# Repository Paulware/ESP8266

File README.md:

ESP8266
=======

All things related to ESP8266 low cost device

ESP8266.ino is a mega sketch to show basic server capability.

Basic theory of UDP operation:
==============================
   Android device sends out a UDP broadcast to local network (i.e. 192.168.0.255).  The message is "findkey" where key is a unique name of the device (i.e. garageDoor).
   
   All units will receive this message but only the unit with the matching key will respond.  The matching unit will respond: "CTS" (clear to send).
   
   When the android device receives this message it now also has the ip address of the device.  All further communication will  be directly from the android device to the specific ip address of the desired unit.

   The unit will now respond to commands, like "open" or "readTemp".

Useful files/directories:
=========================
Schematics/ESP8266Tiny: An Eagle schematic to create a small pcb that holds an atmega328 and ESP8266 connected to D11/D12<br>
The ESP8266 should be running at baud rate 9600.
ssid and password are stored in EEPROM on the atmega328
A serial based menu allows the user to set ssid/password/and unique key which identifies the ESP8266 on the local network

<hr>
<table>
<tr><th>Videos</th></tr>
<tr><td>smart car <a href="https://www.youtube.com/watch?v=Go8Tyr9nKlo&feature=youtu.be">video</a></td></tr>
</table>

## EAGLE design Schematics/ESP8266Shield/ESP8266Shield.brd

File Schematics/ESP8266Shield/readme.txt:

10/23/2014
   Created ready for ordering
11/10/2014
   D0 was driving ESPTX incorrectly.  This was corrected not ordered yet.
1/7/2014
   D12 is now soft-serial receive and D11 is now soft-serial tx
   Have not ordered or verified yet.

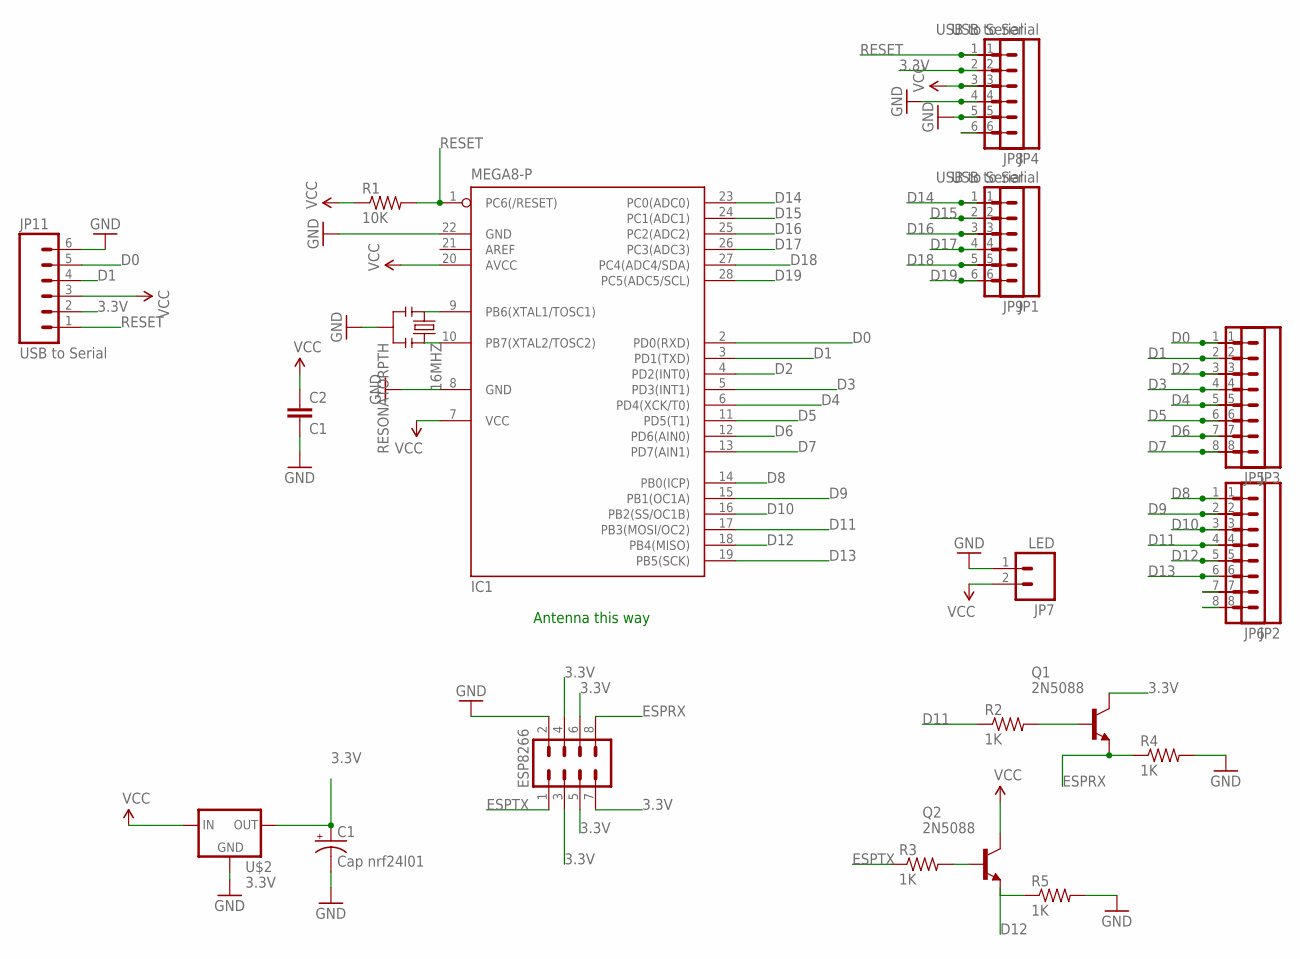
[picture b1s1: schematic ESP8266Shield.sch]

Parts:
16MHZ: RESONATORPTH; RESONATOR-PTH
C1: Cap nrf24l01; CPOL-RADIAL-10UF-25V
C2: C1; CAP-PTH-SMALL
ESP8266: M04X2; 2X4
IC1: MEGA8-P; DIL28-3
JP1, JP4, JP8, JP9, JP11: USB to Serial; 1X06
JP2, JP3, JP5, JP6: M08; 1X08
JP7: LED; 1X02
Q1, Q2: 2N5088; TO92
R1: 10K; AXIAL-0.3
R2, R3, R4, R5: 1K; AXIAL-0.3
U$2: 3.3V; 78XXL

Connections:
3.3V: C1.1 (+), ESP8266.3, ESP8266.4, ESP8266.5, ESP8266.6, ESP8266.7, JP4.2, JP8.2, JP11.2, Q1.1 (C), U$2.GND (OUT)
D0: IC1.2 (PD0(RXD)), JP3.1, JP5.1, JP11.5, Q2.3 (E), R5.P$1 (1)
D1: IC1.3 (PD1(TXD)), JP3.2, JP5.2, JP11.4
D2: IC1.4 (PD2(INT0)), JP3.3, JP5.3
D3: IC1.5 (PD3(INT1)), JP3.4, JP5.4
D4: IC1.6 (PD4(XCK/T0)), JP3.5, JP5.5
D5: IC1.11 (PD5(T1)), JP3.6, JP5.6
D6: IC1.12 (PD6(AIN0)), JP3.7, JP5.7
D7: IC1.13 (PD7(AIN1)), JP3.8, JP5.8
D8: IC1.14 (PB0(ICP)), JP2.1, JP6.1
D9: IC1.15 (PB1(OC1A)), JP2.2, JP6.2
D10: IC1.16 (PB2(SS/OC1B)), JP2.3, JP6.3
D11: IC1.17 (PB3(MOSI/OC2)), JP2.4, JP6.4, R2.P$1 (1)
D12: IC1.18 (PB4(MISO)), JP2.5, JP6.5
D13: IC1.19 (PB5(SCK)), JP2.6, JP6.6
D14: IC1.23 (PC0(ADC0)), JP1.1, JP9.1
D15: IC1.24 (PC1(ADC1)), JP1.2, JP9.2
D16: IC1.25 (PC2(ADC2)), JP1.3, JP9.3
D17: IC1.26 (PC3(ADC3)), JP1.4, JP9.4
D18: IC1.27 (PC4(ADC4/SDA)), JP1.5, JP9.5
D19: IC1.28 (PC5(ADC5/SCL)), JP1.6, JP9.6
ESPRX: ESP8266.8, Q1.3 (E), R4.P$1 (1)
ESPTX: ESP8266.1, R3.P$1 (1)
GND: 16MHZ.2, C1.2 (-), C2.2, ESP8266.2, IC1.8 (GND), IC1.22 (GND), JP4.4, JP4.5, JP7.1, JP8.4, JP8.5, JP11.6, R4.P$2 (2), R5.P$2 (2), U$2.IN (GND)
unnamed: 16MHZ.3, IC1.10 (PB7(XTAL2/TOSC2))
unnamed: 16MHZ.1, IC1.9 (PB6(XTAL1/TOSC1))
unnamed: Q1.2 (B), R2.P$2 (2)
unnamed: Q2.2 (B), R3.P$2 (2)
unnamed: JP2.7, JP6.7
unnamed: JP2.8, JP6.8
unnamed: JP4.6, JP8.6
RESET: IC1.1 (PC6(/RESET)), JP4.1, JP8.1, JP11.1, R1.P$2 (2)
VCC: C2.1, IC1.7 (VCC), IC1.20 (AVCC), JP4.3, JP7.2, JP8.3, JP11.3, Q2.1 (C), R1.P$1 (1), U$2.OUT (IN)

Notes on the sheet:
Antenna this way

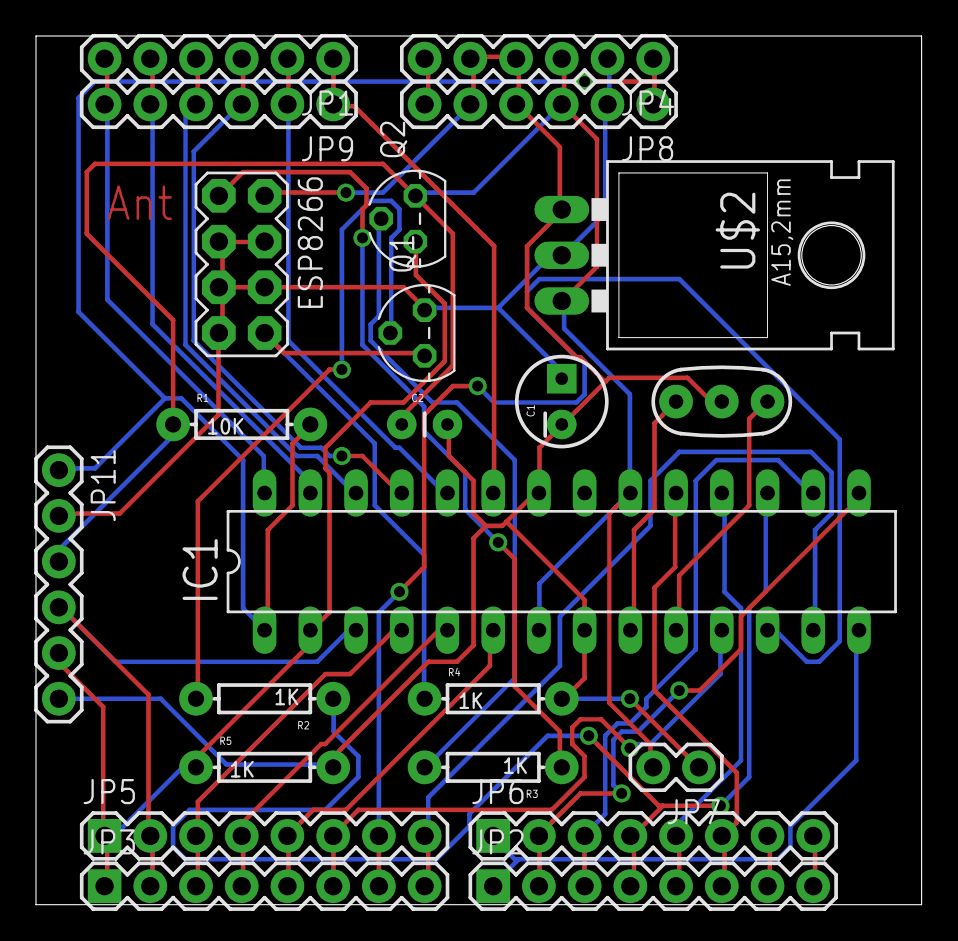
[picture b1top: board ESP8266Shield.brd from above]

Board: 2 copper layers, 49.2 x 48.3 mm, 23 parts (0 on the bottom side), 33 nets.

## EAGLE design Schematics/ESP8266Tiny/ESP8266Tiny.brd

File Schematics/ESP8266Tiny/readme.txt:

10/19/2014
   Created
   Not sure whether the LM 3.3V voltage regulator can provide enough for the ESP8266
   Added a 3.3V Pinout so that an external 3.3V Power source can be provided.
   Will order after testing out the ESP8266 Rx/Tx lines are connected to Arduino
     Rx/Tx so ESP8266 module should be removed will programming.     
   Could be a useful module for an I2C component.
   
10/21/2014
   Confirmed LM 3.3V regulator does indeed provide enough power for this device.
   Transistors were added so that the 5V arduino can communicate with the 3.3V device
   The ESP8266 will need the RX/TX lines, so an I2C component may be necessary
   Go ahead an order the pcb
   
10/22/2014
   PCB ordered from iteadstudio
   
10/23/2014
   Transistor to amplify power to infra-red led with supporting resistors should be
   placed on the main board.  Board ready.  Wait until first board is returned for 
   evaluation before ordering another.
   
11/10/2014
   D0 was driving ESPTX.  (backwards).   Reordering
   
11/18/2014
   AT+CIOBAUD=19200 sets the baud rate to 19200.  This will allow me to communicate with the 
   ESP8266 using soft serial.  Normal Arduino Serial can be used for debugging (better).
   Reordered pcb.  D11 and D12 are now connected to ESP8266
 
12/12/2014
   Redid the .zip file, but this was unnecessary as the last change has not arrived for evaluation yet. 
   
12/31/2014
   Last change arrived (some problem in transportation).
   pcb checks out ok.  Some standoffs would be nice.

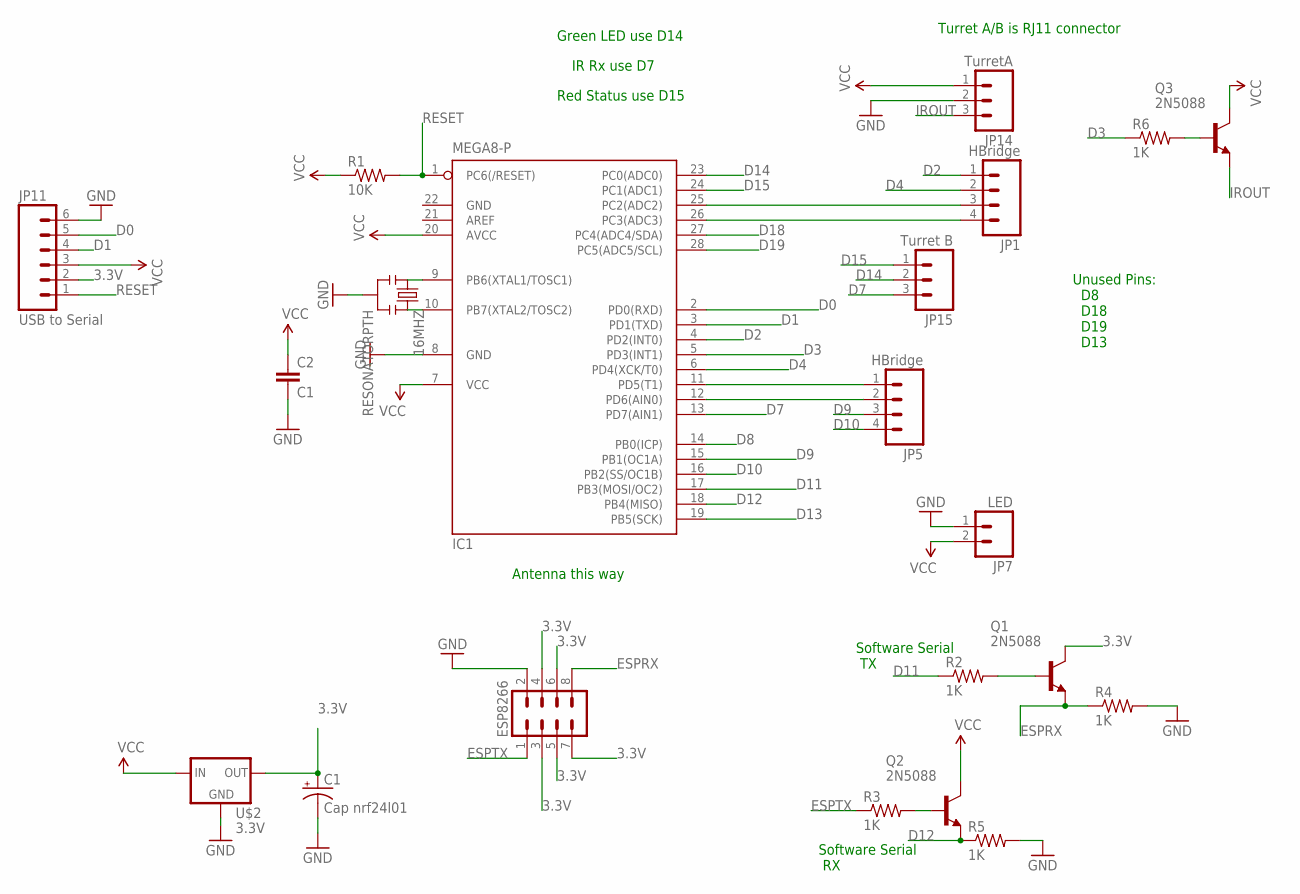
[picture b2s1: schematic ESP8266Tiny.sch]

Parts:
16MHZ: RESONATORPTH; RESONATOR-PTH
C1: Cap nrf24l01; CPOL-RADIAL-10UF-25V
C2: C1; CAP-PTH-SMALL
ESP8266: M04X2; 2X4
IC1: MEGA8-P; DIL28-3
JP1, JP5: HBridge; 1X04
JP7: LED; 1X02
JP11: USB to Serial; 1X06
JP14: TurretA; 1X03
JP15: Turret B; 1X03
Q1, Q2, Q3: 2N5088; TO92
R1: 10K; AXIAL-0.3
R2, R3, R4, R5, R6: 1K; AXIAL-0.3
U$2: 3.3V; 78XXL

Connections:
3.3V: C1.1 (+), ESP8266.3, ESP8266.4, ESP8266.5, ESP8266.6, ESP8266.7, JP11.2, Q1.1 (C), U$2.GND (OUT)
D0: IC1.2 (PD0(RXD)), JP11.5
D1: IC1.3 (PD1(TXD)), JP11.4
D2: IC1.4 (PD2(INT0)), JP1.1
D3: IC1.5 (PD3(INT1)), R6.P$1 (1)
D4: IC1.6 (PD4(XCK/T0)), JP1.2
D7: IC1.13 (PD7(AIN1)), JP15.3
D8: IC1.14 (PB0(ICP))
D9: IC1.15 (PB1(OC1A)), JP5.3
D10: IC1.16 (PB2(SS/OC1B)), JP5.4
D11: IC1.17 (PB3(MOSI/OC2)), R2.P$1 (1)
D12: IC1.18 (PB4(MISO)), Q2.3 (E), R5.P$1 (1)
D13: IC1.19 (PB5(SCK))
D14: IC1.23 (PC0(ADC0)), JP15.2
D15: IC1.24 (PC1(ADC1)), JP15.1
D18: IC1.27 (PC4(ADC4/SDA))
D19: IC1.28 (PC5(ADC5/SCL))
ESPRX: ESP8266.8, Q1.3 (E), R4.P$1 (1)
ESPTX: ESP8266.1, R3.P$1 (1)
GND: 16MHZ.2, C1.2 (-), C2.2, ESP8266.2, IC1.8 (GND), IC1.22 (GND), JP7.1, JP11.6, JP14.2, R4.P$2 (2), R5.P$2 (2), U$2.IN (GND)
IROUT: JP14.3, Q3.3 (E)
unnamed: 16MHZ.3, IC1.10 (PB7(XTAL2/TOSC2))
unnamed: 16MHZ.1, IC1.9 (PB6(XTAL1/TOSC1))
unnamed: Q1.2 (B), R2.P$2 (2)
unnamed: Q2.2 (B), R3.P$2 (2)
unnamed: Q3.2 (B), R6.P$2 (2)
unnamed: IC1.11 (PD5(T1)), JP5.1
unnamed: IC1.25 (PC2(ADC2)), JP1.3
unnamed: IC1.26 (PC3(ADC3)), JP1.4
unnamed: IC1.12 (PD6(AIN0)), JP5.2
RESET: IC1.1 (PC6(/RESET)), JP11.1, R1.P$2 (2)
VCC: C2.1, IC1.7 (VCC), IC1.20 (AVCC), JP7.2, JP11.3, JP14.1, Q2.1 (C), Q3.1 (C), R1.P$1 (1), U$2.OUT (IN)

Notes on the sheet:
Green LED use D14
IR Rx use D7
Red Status use D15
Turret A/B is RJ11 connector
Antenna this way
Unused Pins: D8 D18 D19 D13
Software Serial TX
Software Serial RX

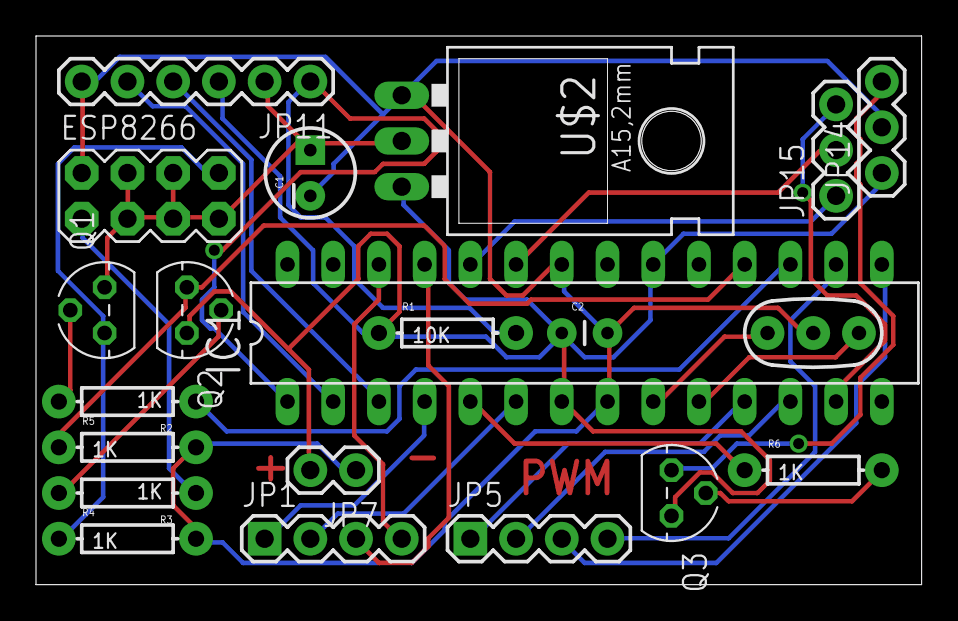
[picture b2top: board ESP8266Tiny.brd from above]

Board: 2 copper layers, 49.2 x 30.5 mm, 21 parts (0 on the bottom side), 28 nets.

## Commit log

2014-10-21 :space_invader: Added .gitattributes & .gitignore files
2014-10-21 v0.01
    Mega sketch to show basic server
2014-10-22 v0.02
    Added a UDP example
2014-10-22 v0.03
    Updated readme for UDP
2014-10-22 v0.04
    Updated readme
2014-10-23 v0.05
    Added Android app source code which communicates which discovers the
    ESP8266 in UDP mode and passes it commands.
2014-10-23 v0.06
    Added an ESP8266 shield (not yet verified)
2014-10-24 v0.06
    Added Shield schematic, and gerber files.
    It has not yet been verified.
2014-10-24 v0.07
    Cleaned up android code
2014-11-18 v0.08
    Updated Android project to close socket on exit
    Updated Arduino projects
2014-11-27 v0.09
    Added CommCheck Arduino program
2014-11-27 V0.10
    Added videos table
2014-12-31 v0.11
    Schematic ESP8266Tiny checked out.
    Updated ESP8266UDP_CommCheck project to work with ESP8266Tiny schematic
2014-12-31 V0.12
    Added .jpg and updated readme
2015-01-07 V0.13
    Updated ESP8266_Shield so that soft-serial can be used.
